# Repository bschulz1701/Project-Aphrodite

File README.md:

# Project-Aphrodite
Designs and software/firmware for custom multi-function motor controller and user interface

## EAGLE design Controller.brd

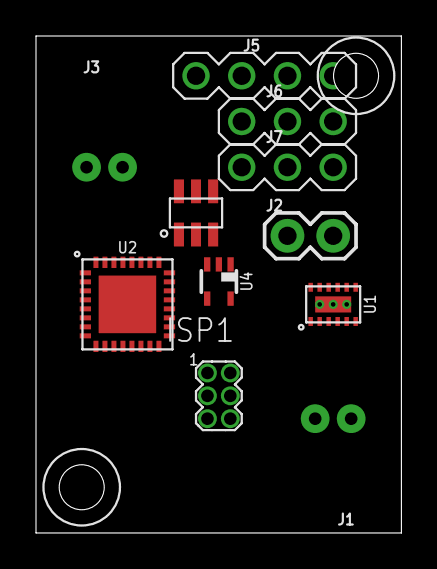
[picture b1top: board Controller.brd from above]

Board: 2 copper layers, 20.3 x 27.6 mm, 13 parts (0 on the bottom side), 3 nets, no tracks yet.

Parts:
H1, H2: 2_56
ISP1: AVRISP1.27MM; 2X3_1.27
J1, J3: JST-2-PTH-NS
J2: 1X02
J5: CONN_42.54; 1X04
J6, J7: CONN_3; 1X03
U1: DRV8839; DSS0012A
U2: ATMEGA328P_TQFPQFN_32; QFN32
U3: 24AA05E; SOT23-6
U4: MIC53653.3SC70; DCK_R-PDSO-G5

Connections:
GND: ISP1.6, U1.5, U1.6, U1.EP@1, U1.EP@2, U1.EP@3, U1.EP@4, U3.2, U4.2
VCC: ISP1.2, U1.12, U3.6
VM: U1.1, U1.2

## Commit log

2019-09-05 Added licence
2019-09-06 Added very initial schematic/layout
